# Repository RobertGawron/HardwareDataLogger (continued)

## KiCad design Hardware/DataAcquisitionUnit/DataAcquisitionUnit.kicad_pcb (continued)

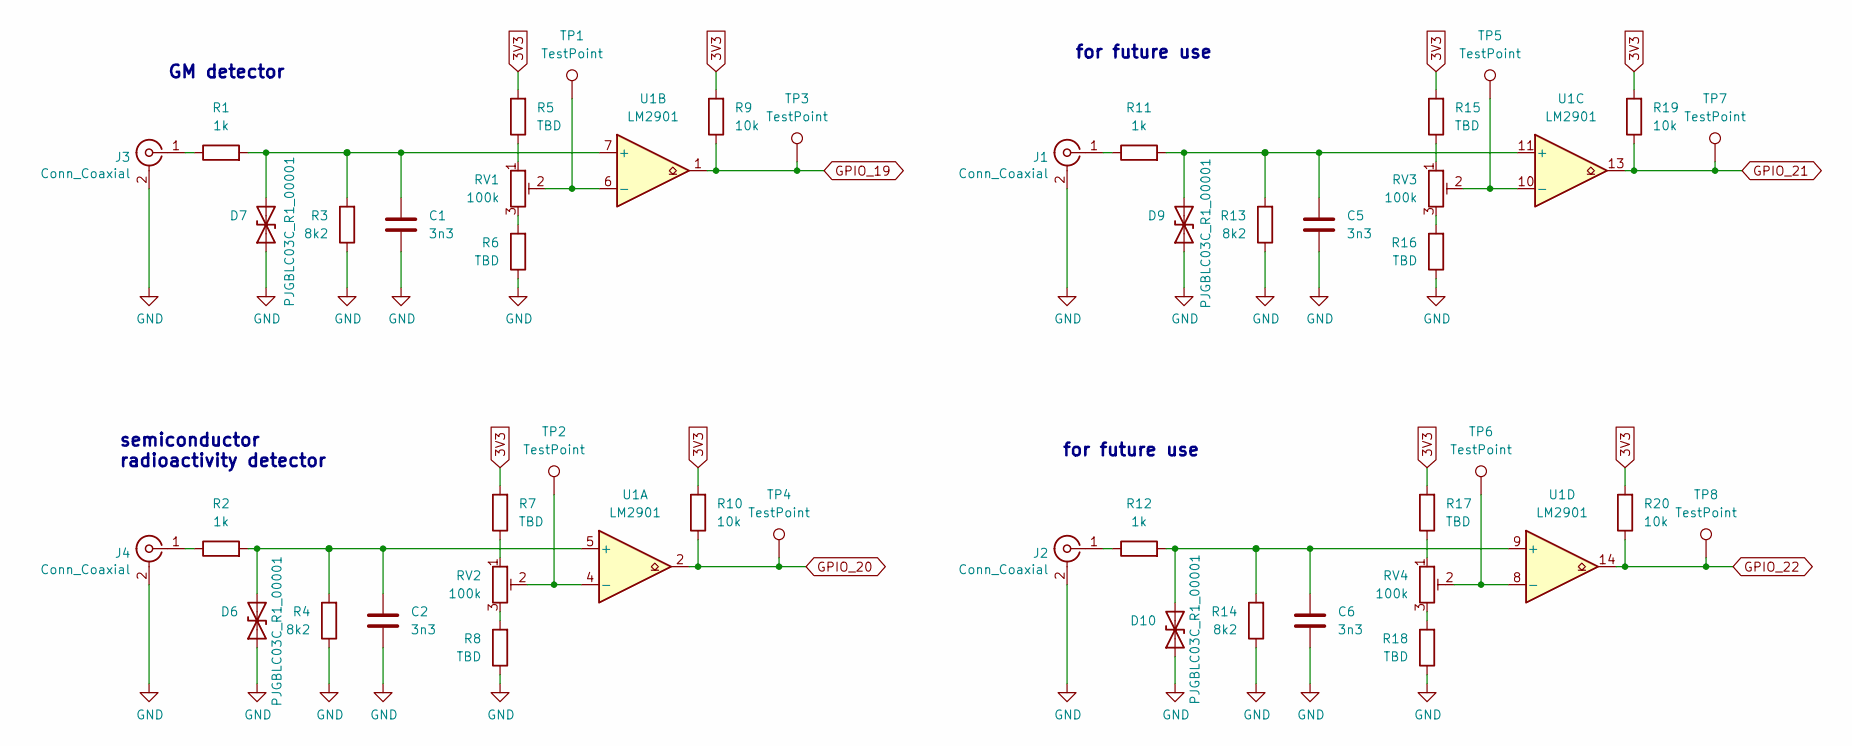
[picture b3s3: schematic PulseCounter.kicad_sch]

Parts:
C1, C2, C5, C6: 3n3; C_0805_2012Metric
D6, D7, D9, D10: PJGBLC03C_R1_00001; D_SOD-323F
J1, J2, J3, J4: Conn_Coaxial; SMA_Molex_73251-2200_Horizontal
R1, R2, R11, R12: 1k; R_0805_2012Metric
R3, R4, R13, R14: 8k2; R_0805_2012Metric
R5, R6, R7, R8, R15, R16, R17, R18: TBD; R_0805_2012Metric
R9, R10, R19, R20: 10k; R_0805_2012Metric
RV1, RV2, RV3, RV4: 100k; Potentiometer_Bourns_3296Y_Vertical
TP1, TP2, TP3, TP4, TP5, TP6, TP7, TP8: TestPoint; TestPoint_Pad_D1.5mm
U1: LM2901; SO-14_3.9x8.65mm_P1.27mm

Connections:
3V3: R5.2, R7.2, R9.2, R10.2, R15.2, R17.2, R19.2, R20.2; also elsewhere on the board
GND: C1.2, C2.2, C5.2, C6.2, D6.1 (A1), D7.1 (A1), D9.1 (A1), D10.1 (A1), J1.2 (Ext), J2.2 (Ext), J3.2 (Ext), J4.2 (Ext), R3.1, R4.1, R6.1, R8.1, R13.1, R14.1, R16.1, R18.1; also elsewhere on the board
GPIO_19: R9.1, TP3.1, U1.1; also elsewhere on the board
GPIO_20: R10.1, TP4.1, U1.2; also elsewhere on the board
GPIO_21: R19.1, TP7.1, U1.13; also elsewhere on the board
GPIO_22: R20.1, TP8.1, U1.14; also elsewhere on the board
unnamed: C2.1, D6.2 (A2), R2.2, R4.2, U1.5 (+)
unnamed: C1.1, D7.2 (A2), R1.2, R3.2, U1.7 (+)
unnamed: C5.1, D9.2 (A2), R11.2, R13.2, U1.11 (+)
unnamed: C6.1, D10.2 (A2), R12.2, R14.2, U1.9 (+)
unnamed: J1.1 (In), R11.1
unnamed: J2.1 (In), R12.1
unnamed: J3.1 (In), R1.1
unnamed: J4.1 (In), R2.1
unnamed: R5.1, RV1.1
unnamed: R6.2, RV1.3
unnamed: R7.1, RV2.1
unnamed: R8.2, RV2.3
unnamed: R15.1, RV3.1
unnamed: R16.2, RV3.3
unnamed: R17.1, RV4.1
unnamed: R18.2, RV4.3
unnamed: RV2.2, TP2.1, U1.4 (-)
unnamed: RV1.2, TP1.1, U1.6 (-)
unnamed: RV3.2, TP5.1, U1.10 (-)
unnamed: RV4.2, TP6.1, U1.8 (-)

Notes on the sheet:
GM detector
for future use
semiconductor radioactivity detector

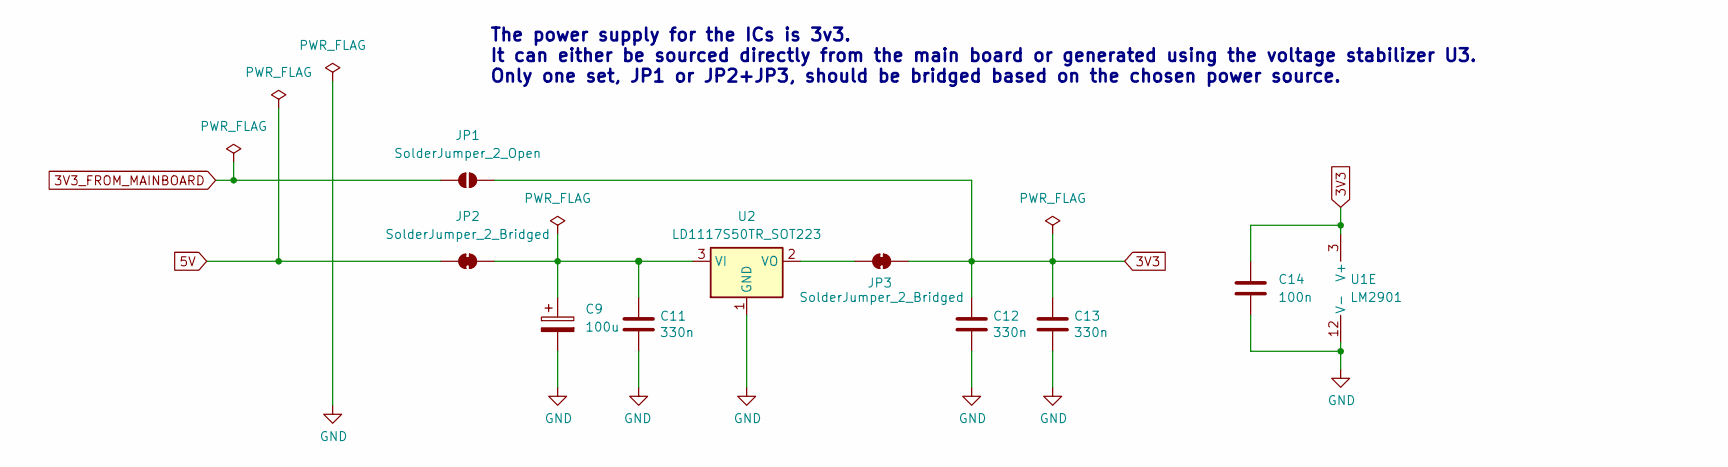
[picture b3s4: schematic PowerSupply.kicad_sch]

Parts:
C9: 100u; CP_Elec_6.3x5.8
C11, C12, C13: 330n; C_0805_2012Metric
C14: 100n; C_0805_2012Metric
JP1: SolderJumper_2_Open; SolderJumper-2_P1.3mm_Open_Pad1.0x1.5mm
JP2, JP3: SolderJumper_2_Bridged; SolderJumper-2_P1.3mm_Bridged_Pad1.0x1.5mm
U1: LM2901; SO-14_3.9x8.65mm_P1.27mm
U2: LD1117S50TR_SOT223; SOT-223-3_TabPin2

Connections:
3V3: C12.1, C13.1, C14.1, JP1.2 (B), JP3.2 (B), U1.3 (V+); also elsewhere on the board
3V3_FROM_MAINBOARD: JP1.1 (A); also elsewhere on the board
5V: JP2.1 (A); also elsewhere on the board
GND: C9.2, C11.2, C12.2, C13.2, C14.2, U1.12 (V-), U2.1 (GND); also elsewhere on the board
unnamed: C9.1, C11.1, JP2.2 (B), U2.3 (VI)
unnamed: JP3.1 (A), U2.2 (VO)

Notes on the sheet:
The power supply for the ICs is 3v3. It can either be sourced directly from the main board or generated using the voltage stabilizer U3. Only one set, JP1 or JP2+JP3, should be bridged based on the chosen power source.

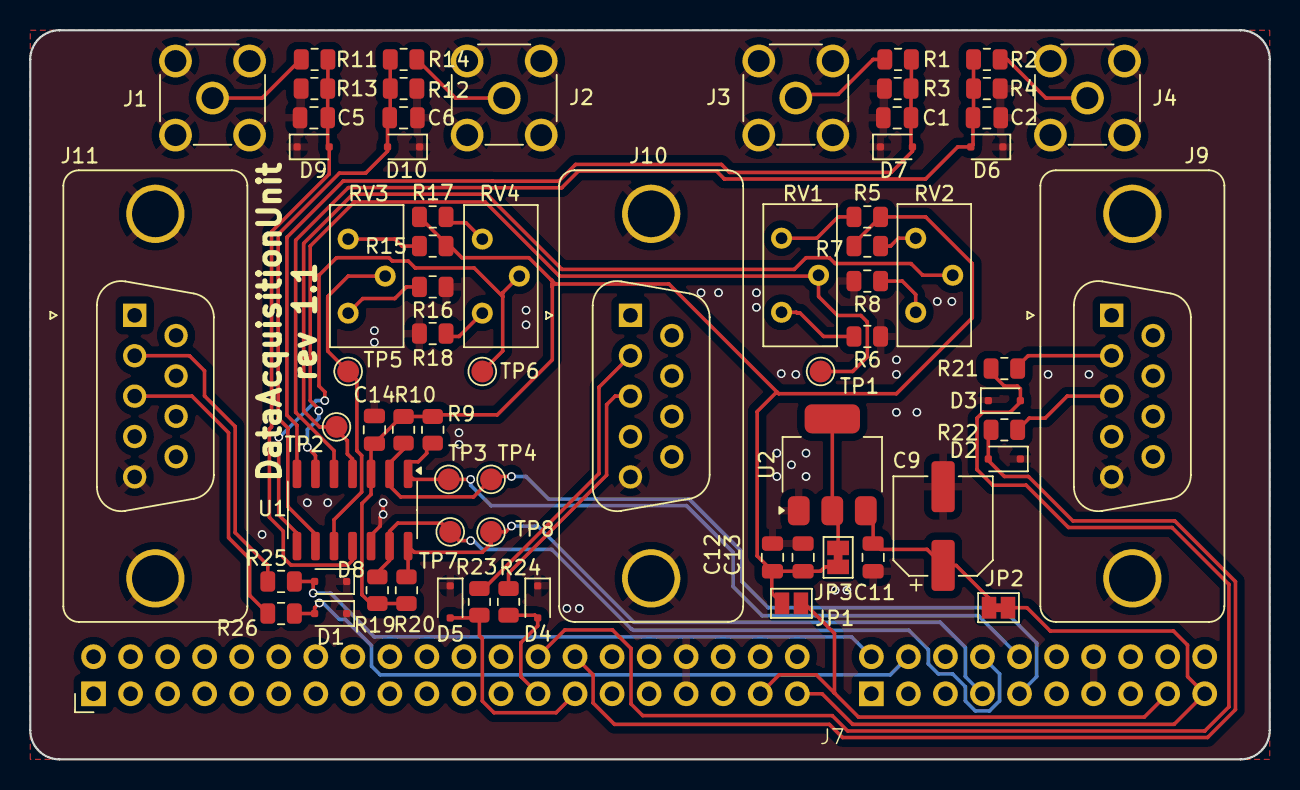
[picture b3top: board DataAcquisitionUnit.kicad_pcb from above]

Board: 2 copper layers, 85.0 x 50.0 mm, 70 parts (0 on the bottom side), 42 nets.

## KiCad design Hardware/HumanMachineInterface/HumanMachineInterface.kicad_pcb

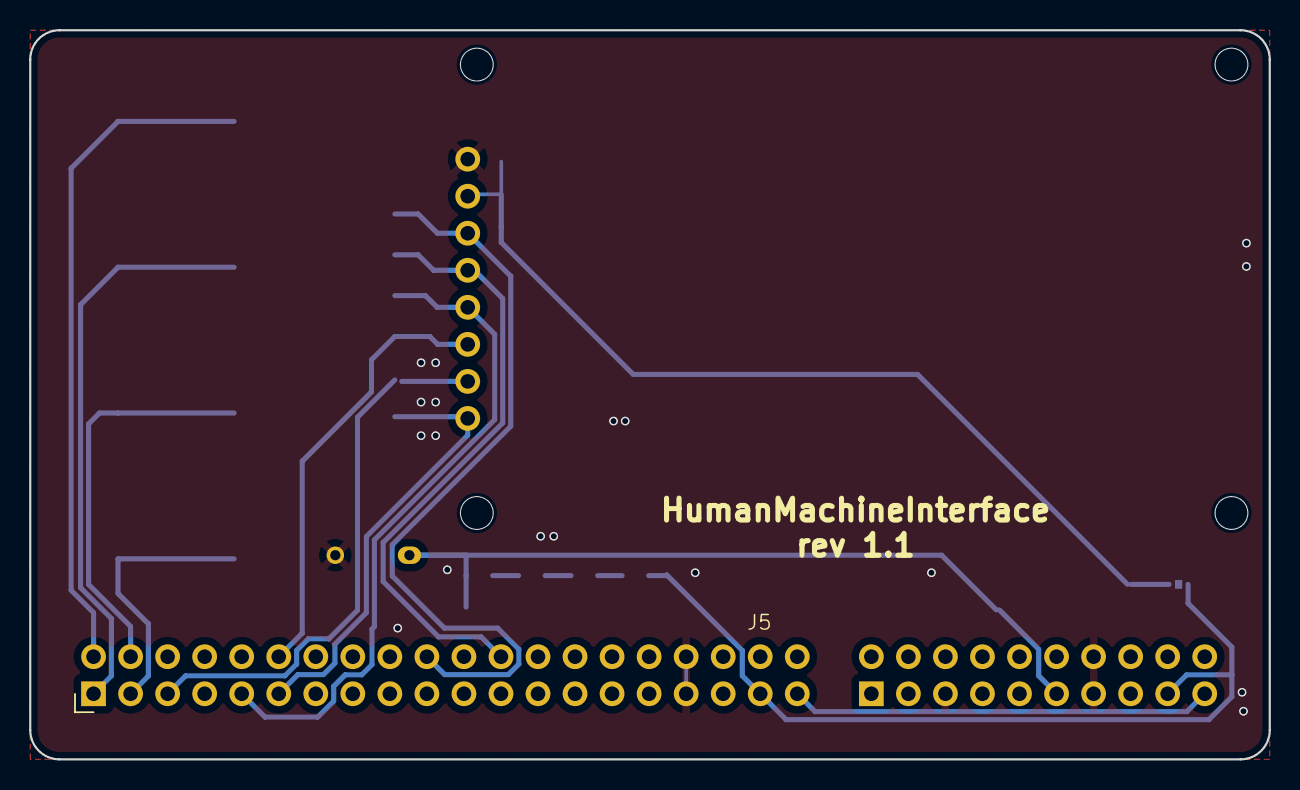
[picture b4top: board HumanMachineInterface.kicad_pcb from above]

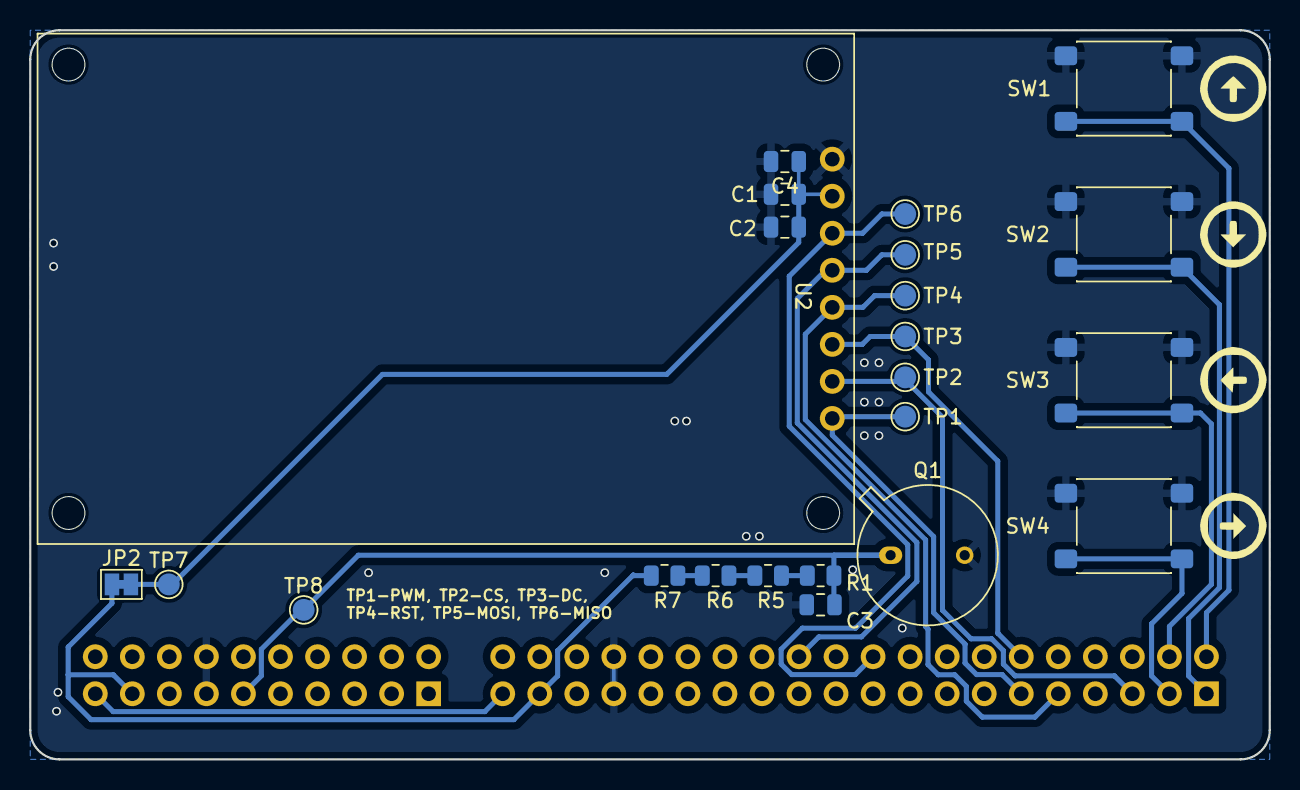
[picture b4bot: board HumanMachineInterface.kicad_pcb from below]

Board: 2 copper layers, 85.0 x 50.0 mm, 24 parts (23 on the bottom side), 18 nets.

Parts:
C1, C4: 4u7; C_0805_2012Metric
C2, C3: 330n; C_0805_2012Metric
J5: ExtensionConnector
JP2: SolderJumper_2_Bridged; SolderJumper-2_P1.3mm_Bridged_Pad1.0x1.5mm
Q1: Q_Photo_NPN; TO-5-2
R1, R5, R6, R7: 1M; R_0805_2012Metric
SW1, SW2, SW3, SW4: SW_Push; SW_SPST_PTS645Sx43SMTR92
TP1, TP2, TP3, TP4, TP5, TP6, TP7, TP8: TestPoint; TestPoint_Pad_D1.5mm
U2: ST7735S

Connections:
3V3_FROM_MAINBOARD: J5.37, J5.57, JP2.1 (A), R7.1
5V: J5.39, J5.59
GND: C1.2, C2.2, C3.2, C4.2, J5.33, J5.34, J5.45, J5.53, J5.54, Q1.2 (E), SW1.1, SW2.1, SW3.1, SW4.1, U2.1 (GND)
GPIO_5: J5.12, TP3.1, U2.6 (DC)
GPIO_6: J5.11, TP1.1, U2.8 (BL)
GPIO_8: J5.9, TP4.1, U2.5 (RES)
GPIO_12: J5.5, TP2.1, U2.7 (CS)
GPIO_13: J5.4, SW3.2
GPIO_14: J5.3, SW4.2
GPIO_15: J5.2, SW1.2
GPIO_16: J5.1, SW2.2
GPIO_18: C3.1, J5.51, Q1.1 (C), R1.2, TP8.1
unnamed: C1.1, C2.1, C4.1, JP2.2 (B), TP7.1, U2.2 (VCC)
unnamed: R1.1, R5.2
unnamed: R5.1, R6.2
unnamed: R6.1, R7.2
SPI1_MOSI: J5.24, TP5.1, U2.4 (SDA)
SPI1_SCK: J5.20, TP6.1, U2.3 (SCL)

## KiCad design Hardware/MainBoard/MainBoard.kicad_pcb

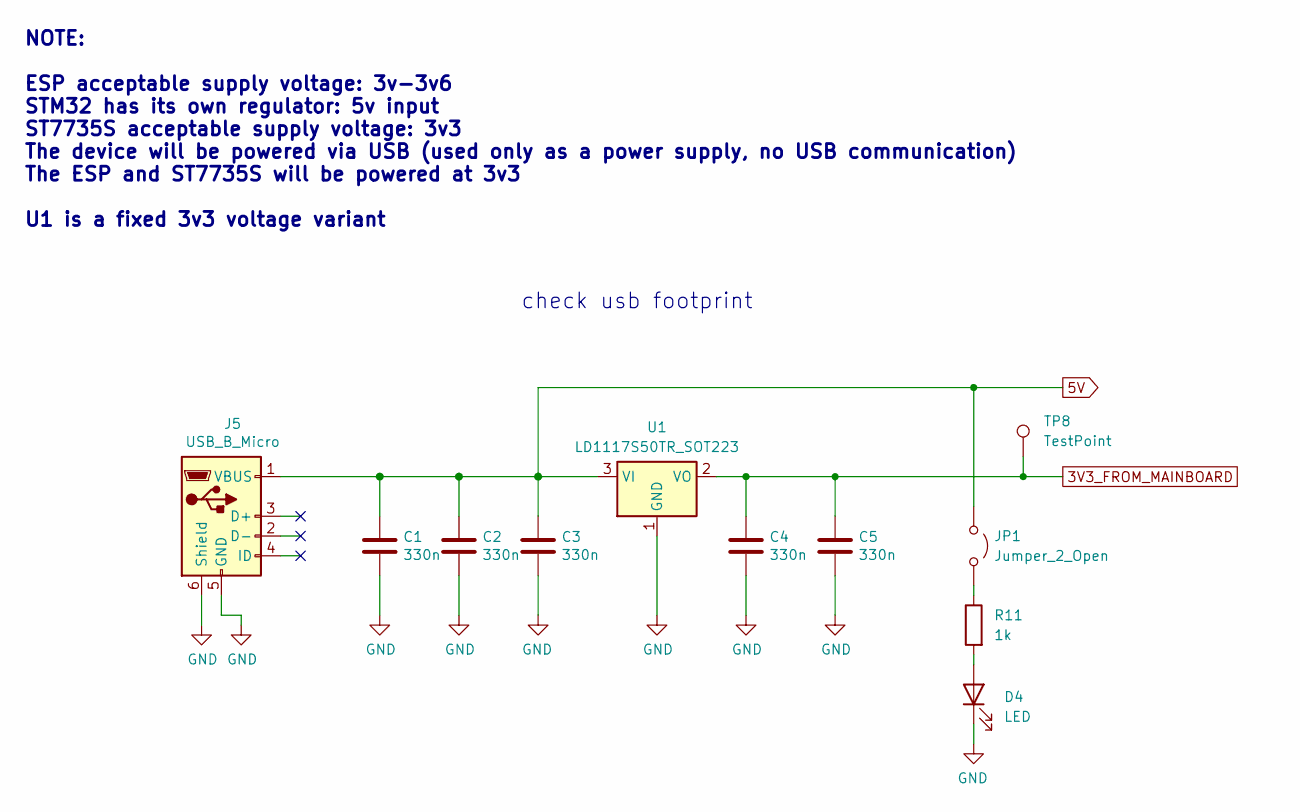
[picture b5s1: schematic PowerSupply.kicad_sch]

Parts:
C1, C2, C3, C4, C5: 330n; C_0805_2012Metric
D4: LED; LED_0402_1005Metric
J5: USB_B_Micro; USB_Micro-B_Molex-105017-0001_Extra_Mechanical_Pads
JP1: Jumper_2_Open; PinHeader_1x02_P2.54mm_Vertical
R11: 1k; R_0805_2012Metric
TP8: TestPoint; TestPoint_Pad_D1.5mm
U1: LD1117S50TR_SOT223; SOT-223-3_TabPin2

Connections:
3V3_FROM_MAINBOARD: C4.1, C5.1, TP8.1, U1.2 (VO); also elsewhere on the board
5V: C1.1, C2.1, C3.1, J5.1 (VBUS), JP1.1 (A), U1.3 (VI); also elsewhere on the board
GND: C1.2, C2.2, C3.2, C4.2, C5.2, D4.1 (K), J5.5 (GND), J5.6 (Shield), U1.1 (GND); also elsewhere on the board
unnamed: D4.2 (A), R11.2
unnamed: JP1.2 (B), R11.1

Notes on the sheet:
NOTE: ESP acceptable supply voltage: 3v-3v6 STM32 has its own regulator: 5v input ST7735S acceptable supply voltage: 3v3 The device will be powered via USB (used only as a power supply, no USB communication) The ESP and ST7735S will be powered at 3v3 U1 is a fixed 3v3 voltage variant
check usb footprint

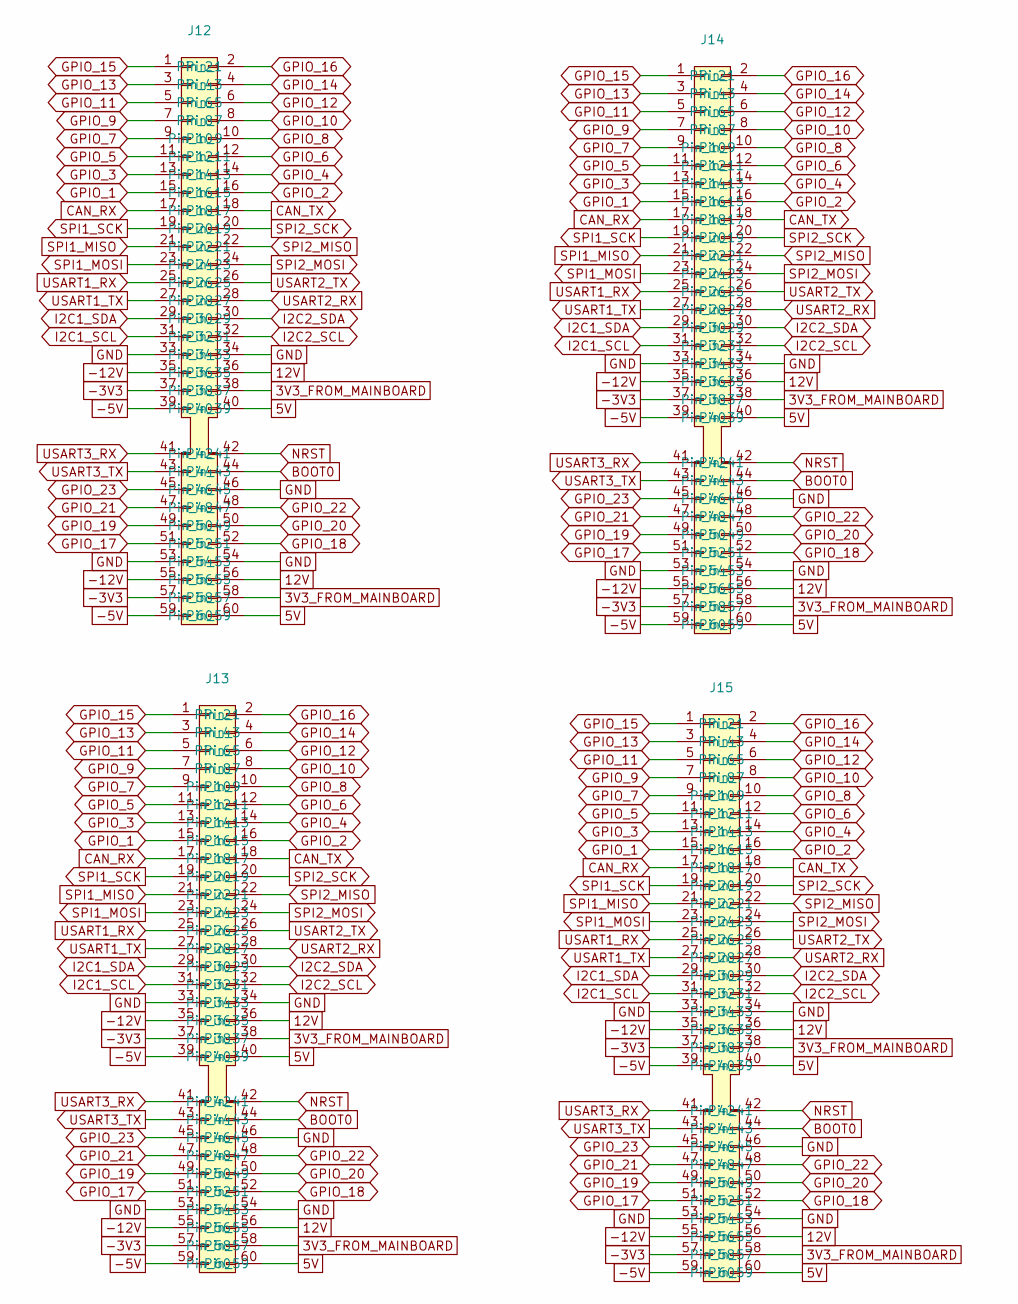
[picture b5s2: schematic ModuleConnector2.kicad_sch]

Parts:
J12, J13, J14, J15: ExtensionConnector

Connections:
3V3_FROM_MAINBOARD: J12.38, J12.58, J13.38, J13.58, J14.38, J14.58, J15.38, J15.58; also elsewhere on the board
5V: J12.40, J12.60, J13.40, J13.60, J14.40, J14.60, J15.40, J15.60; also elsewhere on the board
12V: J12.36, J12.56, J13.36, J13.56, J14.36, J14.56, J15.36, J15.56; also elsewhere on the board
-3V3: J12.37, J12.57, J13.37, J13.57, J14.37, J14.57, J15.37, J15.57; also elsewhere on the board
-5V: J12.39, J12.59, J13.39, J13.59, J14.39, J14.59, J15.39, J15.59; also elsewhere on the board
-12V: J12.35, J12.55, J13.35, J13.55, J14.35, J14.55, J15.35, J15.55; also elsewhere on the board
BOOT0: J12.44, J13.44, J14.44, J15.44; also elsewhere on the board
CAN_RX: J12.17, J13.17, J14.17, J15.17; also elsewhere on the board
CAN_TX: J12.18, J13.18, J14.18, J15.18; also elsewhere on the board
GND: J12.33, J12.34, J12.46, J12.53, J12.54, J13.33, J13.34, J13.46, J13.53, J13.54, J14.33, J14.34, J14.46, J14.53, J14.54, J15.33, J15.34, J15.46, J15.53, J15.54; also elsewhere on the board
GPIO_1: J12.15, J13.15, J14.15, J15.15; also elsewhere on the board
GPIO_2: J12.16, J13.16, J14.16, J15.16; also elsewhere on the board
GPIO_3: J12.13, J13.13, J14.13, J15.13; also elsewhere on the board
GPIO_4: J12.14, J13.14, J14.14, J15.14; also elsewhere on the board
GPIO_5: J12.11, J13.11, J14.11, J15.11; also elsewhere on the board
GPIO_6: J12.12, J13.12, J14.12, J15.12; also elsewhere on the board
GPIO_7: J12.9, J13.9, J14.9, J15.9; also elsewhere on the board
GPIO_8: J12.10, J13.10, J14.10, J15.10; also elsewhere on the board
GPIO_9: J12.7, J13.7, J14.7, J15.7; also elsewhere on the board
GPIO_10: J12.8, J13.8, J14.8, J15.8; also elsewhere on the board
GPIO_11: J12.5, J13.5, J14.5, J15.5; also elsewhere on the board
GPIO_12: J12.6, J13.6, J14.6, J15.6; also elsewhere on the board
GPIO_13: J12.3, J13.3, J14.3, J15.3; also elsewhere on the board
GPIO_14: J12.4, J13.4, J14.4, J15.4; also elsewhere on the board
GPIO_15: J12.1, J13.1, J14.1, J15.1; also elsewhere on the board
GPIO_16: J12.2, J13.2, J14.2, J15.2; also elsewhere on the board
GPIO_17: J12.51, J13.51, J14.51, J15.51; also elsewhere on the board
GPIO_18: J12.52, J13.52, J14.52, J15.52; also elsewhere on the board
GPIO_19: J12.49, J13.49, J14.49, J15.49; also elsewhere on the board
GPIO_20: J12.50, J13.50, J14.50, J15.50; also elsewhere on the board
GPIO_21: J12.47, J13.47, J14.47, J15.47; also elsewhere on the board
GPIO_22: J12.48, J13.48, J14.48, J15.48; also elsewhere on the board
GPIO_23: J12.45, J13.45, J14.45, J15.45; also elsewhere on the board
I2C1_SCL: J12.31, J13.31, J14.31, J15.31; also elsewhere on the board
I2C1_SDA: J12.29, J13.29, J14.29, J15.29; also elsewhere on the board
I2C2_SCL: J12.32, J13.32, J14.32, J15.32; also elsewhere on the board
I2C2_SDA: J12.30, J13.30, J14.30, J15.30; also elsewhere on the board
NRST: J12.42, J13.42, J14.42, J15.42; also elsewhere on the board
SPI1_MISO: J12.21, J13.21, J14.21, J15.21; also elsewhere on the board
SPI1_MOSI: J12.23, J13.23, J14.23, J15.23; also elsewhere on the board
SPI1_SCK: J12.19, J13.19, J14.19, J15.19; also elsewhere on the board
SPI2_MISO: J12.22, J13.22, J14.22, J15.22; also elsewhere on the board
SPI2_MOSI: J12.24, J13.24, J14.24, J15.24; also elsewhere on the board
SPI2_SCK: J12.20, J13.20, J14.20, J15.20; also elsewhere on the board
USART1_RX: J12.25, J13.25, J14.25, J15.25; also elsewhere on the board
USART1_TX: J12.27, J13.27, J14.27, J15.27; also elsewhere on the board
USART2_RX: J12.28, J13.28, J14.28, J15.28; also elsewhere on the board
USART2_TX: J12.26, J13.26, J14.26, J15.26; also elsewhere on the board
USART3_RX: J12.41, J13.41, J14.41, J15.41; also elsewhere on the board
USART3_TX: J12.43, J13.43, J14.43, J15.43; also elsewhere on the board

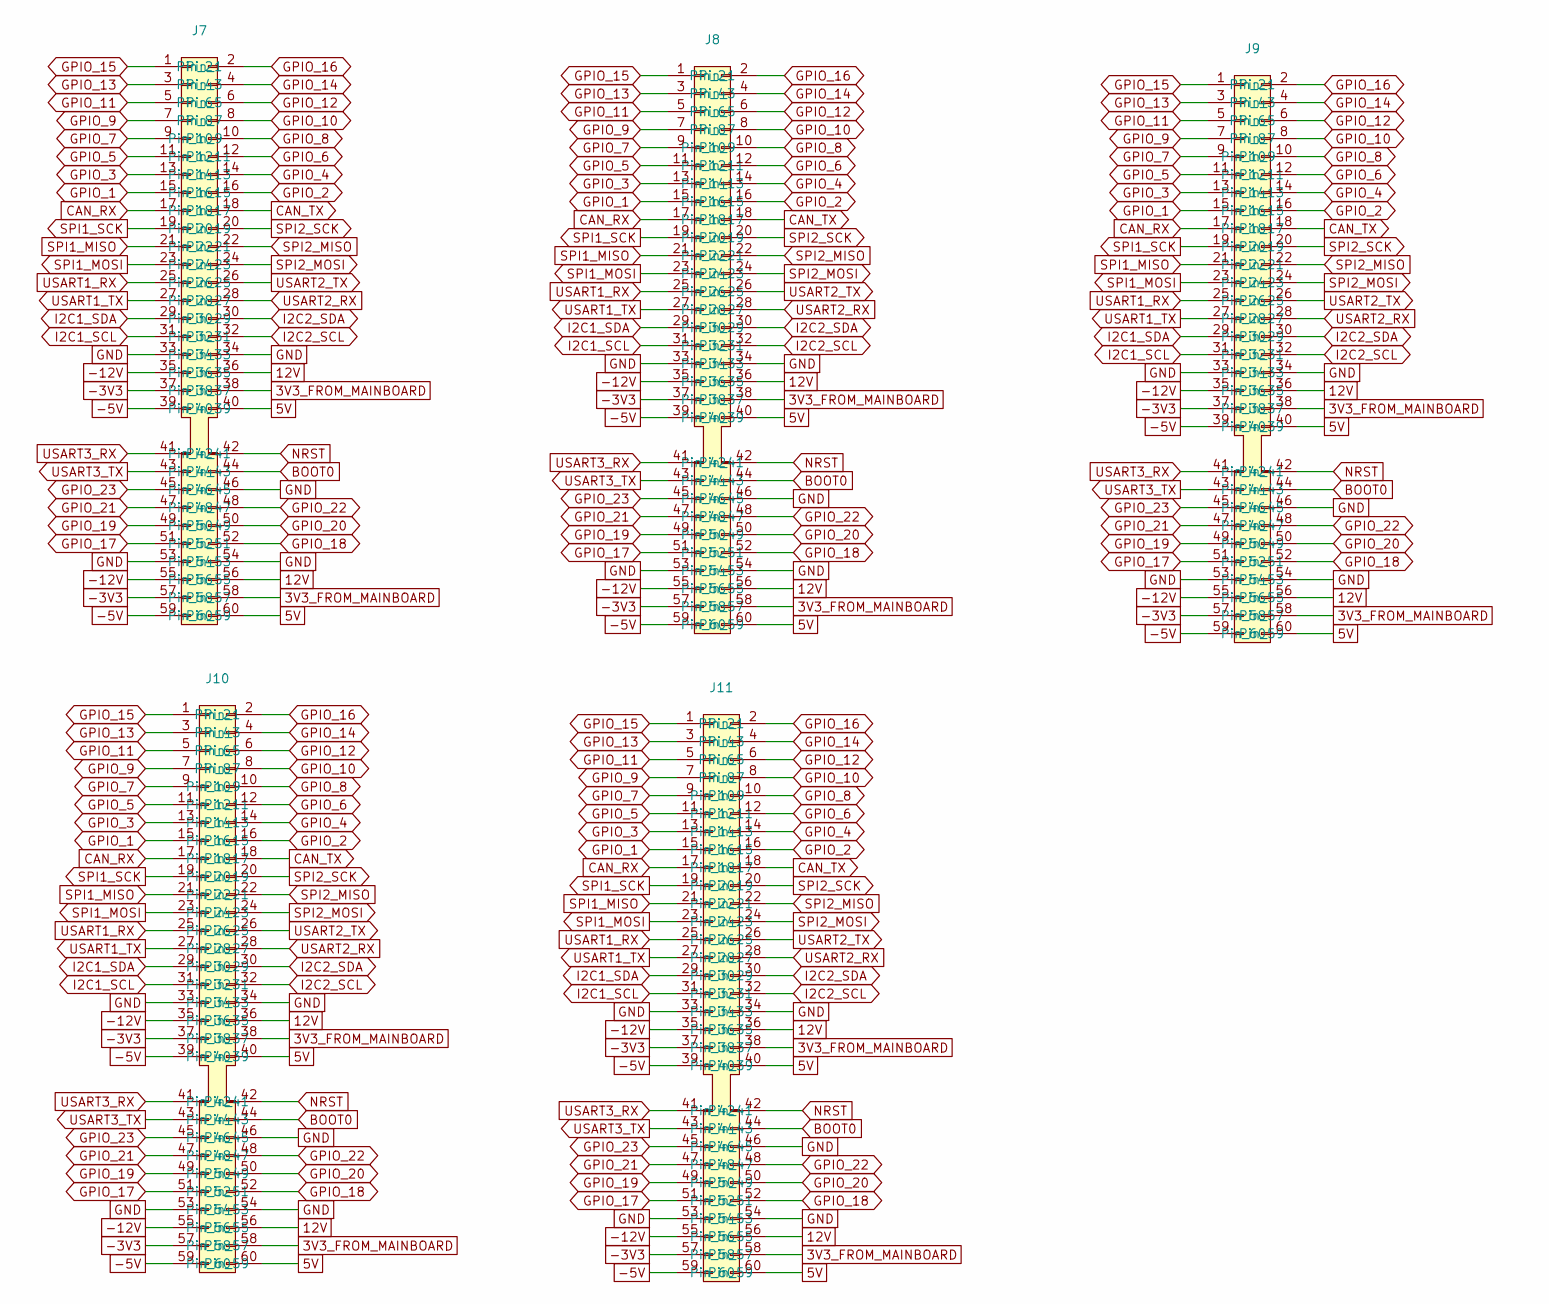
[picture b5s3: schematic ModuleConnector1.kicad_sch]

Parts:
J7, J8, J9, J10, J11: ExtensionConnector

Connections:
3V3_FROM_MAINBOARD: J7.38, J7.58, J8.38, J8.58, J9.38, J9.58, J10.38, J10.58, J11.38, J11.58; also elsewhere on the board
5V: J7.40, J7.60, J8.40, J8.60, J9.40, J9.60, J10.40, J10.60, J11.40, J11.60; also elsewhere on the board
12V: J7.36, J7.56, J8.36, J8.56, J9.36, J9.56, J10.36, J10.56, J11.36, J11.56; also elsewhere on the board
-3V3: J7.37, J7.57, J8.37, J8.57, J9.37, J9.57, J10.37, J10.57, J11.37, J11.57; also elsewhere on the board
-5V: J7.39, J7.59, J8.39, J8.59, J9.39, J9.59, J10.39, J10.59, J11.39, J11.59; also elsewhere on the board
-12V: J7.35, J7.55, J8.35, J8.55, J9.35, J9.55, J10.35, J10.55, J11.35, J11.55; also elsewhere on the board
BOOT0: J7.44, J8.44, J9.44, J10.44, J11.44; also elsewhere on the board
CAN_RX: J7.17, J8.17, J9.17, J10.17, J11.17; also elsewhere on the board
CAN_TX: J7.18, J8.18, J9.18, J10.18, J11.18; also elsewhere on the board
GND: J7.33, J7.34, J7.46, J7.53, J7.54, J8.33, J8.34, J8.46, J8.53, J8.54, J9.33, J9.34, J9.46, J9.53, J9.54, J10.33, J10.34, J10.46, J10.53, J10.54, J11.33, J11.34, J11.46, J11.53, J11.54; also elsewhere on the board
GPIO_1: J7.15, J8.15, J9.15, J10.15, J11.15; also elsewhere on the board
GPIO_2: J7.16, J8.16, J9.16, J10.16, J11.16; also elsewhere on the board
GPIO_3: J7.13, J8.13, J9.13, J10.13, J11.13; also elsewhere on the board
GPIO_4: J7.14, J8.14, J9.14, J10.14, J11.14; also elsewhere on the board
GPIO_5: J7.11, J8.11, J9.11, J10.11, J11.11; also elsewhere on the board
GPIO_6: J7.12, J8.12, J9.12, J10.12, J11.12; also elsewhere on the board
GPIO_7: J7.9, J8.9, J9.9, J10.9, J11.9; also elsewhere on the board
GPIO_8: J7.10, J8.10, J9.10, J10.10, J11.10; also elsewhere on the board
GPIO_9: J7.7, J8.7, J9.7, J10.7, J11.7; also elsewhere on the board
GPIO_10: J7.8, J8.8, J9.8, J10.8, J11.8; also elsewhere on the board
GPIO_11: J7.5, J8.5, J9.5, J10.5, J11.5; also elsewhere on the board
GPIO_12: J7.6, J8.6, J9.6, J10.6, J11.6; also elsewhere on the board
GPIO_13: J7.3, J8.3, J9.3, J10.3, J11.3; also elsewhere on the board
GPIO_14: J7.4, J8.4, J9.4, J10.4, J11.4; also elsewhere on the board
GPIO_15: J7.1, J8.1, J9.1, J10.1, J11.1; also elsewhere on the board
GPIO_16: J7.2, J8.2, J9.2, J10.2, J11.2; also elsewhere on the board
GPIO_17: J7.51, J8.51, J9.51, J10.51, J11.51; also elsewhere on the board
GPIO_18: J7.52, J8.52, J9.52, J10.52, J11.52; also elsewhere on the board
GPIO_19: J7.49, J8.49, J9.49, J10.49, J11.49; also elsewhere on the board
GPIO_20: J7.50, J8.50, J9.50, J10.50, J11.50; also elsewhere on the board
GPIO_21: J7.47, J8.47, J9.47, J10.47, J11.47; also elsewhere on the board
GPIO_22: J7.48, J8.48, J9.48, J10.48, J11.48; also elsewhere on the board
GPIO_23: J7.45, J8.45, J9.45, J10.45, J11.45; also elsewhere on the board
I2C1_SCL: J7.31, J8.31, J9.31, J10.31, J11.31; also elsewhere on the board
I2C1_SDA: J7.29, J8.29, J9.29, J10.29, J11.29; also elsewhere on the board
I2C2_SCL: J7.32, J8.32, J9.32, J10.32, J11.32; also elsewhere on the board
I2C2_SDA: J7.30, J8.30, J9.30, J10.30, J11.30; also elsewhere on the board
NRST: J7.42, J8.42, J9.42, J10.42, J11.42; also elsewhere on the board
SPI1_MISO: J7.21, J8.21, J9.21, J10.21, J11.21; also elsewhere on the board
SPI1_MOSI: J7.23, J8.23, J9.23, J10.23, J11.23; also elsewhere on the board
SPI1_SCK: J7.19, J8.19, J9.19, J10.19, J11.19; also elsewhere on the board
SPI2_MISO: J7.22, J8.22, J9.22, J10.22, J11.22; also elsewhere on the board
SPI2_MOSI: J7.24, J8.24, J9.24, J10.24, J11.24; also elsewhere on the board
SPI2_SCK: J7.20, J8.20, J9.20, J10.20, J11.20; also elsewhere on the board
USART1_RX: J7.25, J8.25, J9.25, J10.25, J11.25; also elsewhere on the board
USART1_TX: J7.27, J8.27, J9.27, J10.27, J11.27; also elsewhere on the board
USART2_RX: J7.28, J8.28, J9.28, J10.28, J11.28; also elsewhere on the board
USART2_TX: J7.26, J8.26, J9.26, J10.26, J11.26; also elsewhere on the board
USART3_RX: J7.41, J8.41, J9.41, J10.41, J11.41; also elsewhere on the board
USART3_TX: J7.43, J8.43, J9.43, J10.43, J11.43; also elsewhere on the board

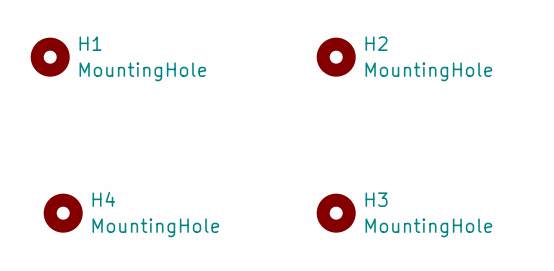
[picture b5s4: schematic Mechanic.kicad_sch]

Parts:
H1, H2, H3, H4: MountingHole; MountingHole_3.5mm

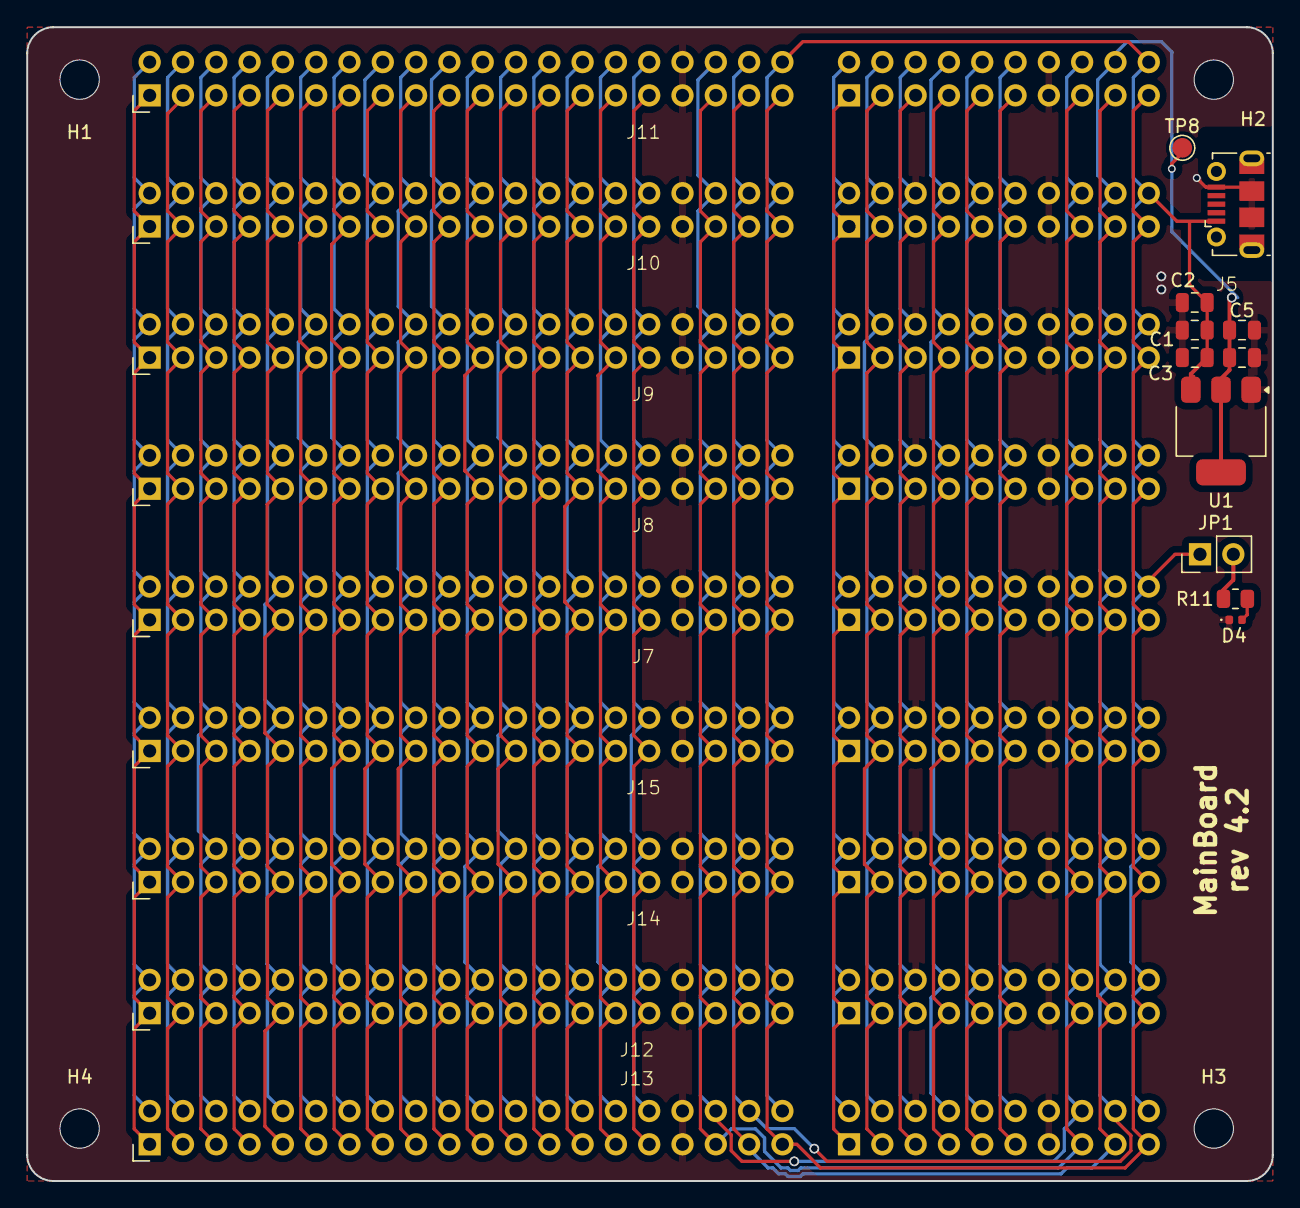
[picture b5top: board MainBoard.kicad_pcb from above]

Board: 2 copper layers, 95.0 x 88.0 mm, 24 parts (0 on the bottom side), 52 nets.
